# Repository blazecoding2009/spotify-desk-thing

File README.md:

# spotify desk thing
### custom made pcb to be like the [spotify car thing](https://support.spotify.com/us/article/car-thing-discontinued/) (sadly discontinued)

yeah this is something i literally thought of while sitting and listening to music and i think it'd look cool lol
the whole project is pretty self-explanatory, a replacement to the spotify desk think, you could use this as a deskpad with diff firmware too!!

## Features

- ESP32-S3
- 3.5” 480×320 SPI TFT display
- Capacitive touchscreen (GT911)
- SD card music playback
- I²S DAC (PCM5242)
- Differential headphone amp (TPA6132A2)
- Rotary encoder for volume + play/pause
- Headphone output (3.5mm jack)

---

## Hardware Overview

### Main Components

- **ESP32-S3-WROOM-1**
- **ST7796 3.5” TFT Display**
- **GT911 Capacitive Touch (on display)**
- **PCM5242 DAC**
- **TPA6132A2 Headphone Amplifier**
- **MicroSD Card **
- **Rotary Encoder with push button**

## Firmware Overview

The firmware is written using **ESP-IDF**.

### Tasks

- **UI Task**
  - Draws the interface
  - Handles play/pause and volume updates

- **Input Task**
  - Reads touch input
  - Reads rotary encoder events
  - Pushes events into a queue

- **Audio Task**
  - Plays WAV files
  - Handles beeps and stop commands
 
## Future Ideas

- Spotify / Wi-Fi streaming
- Album art
- Playlists
- Battery power
- Better UI animations

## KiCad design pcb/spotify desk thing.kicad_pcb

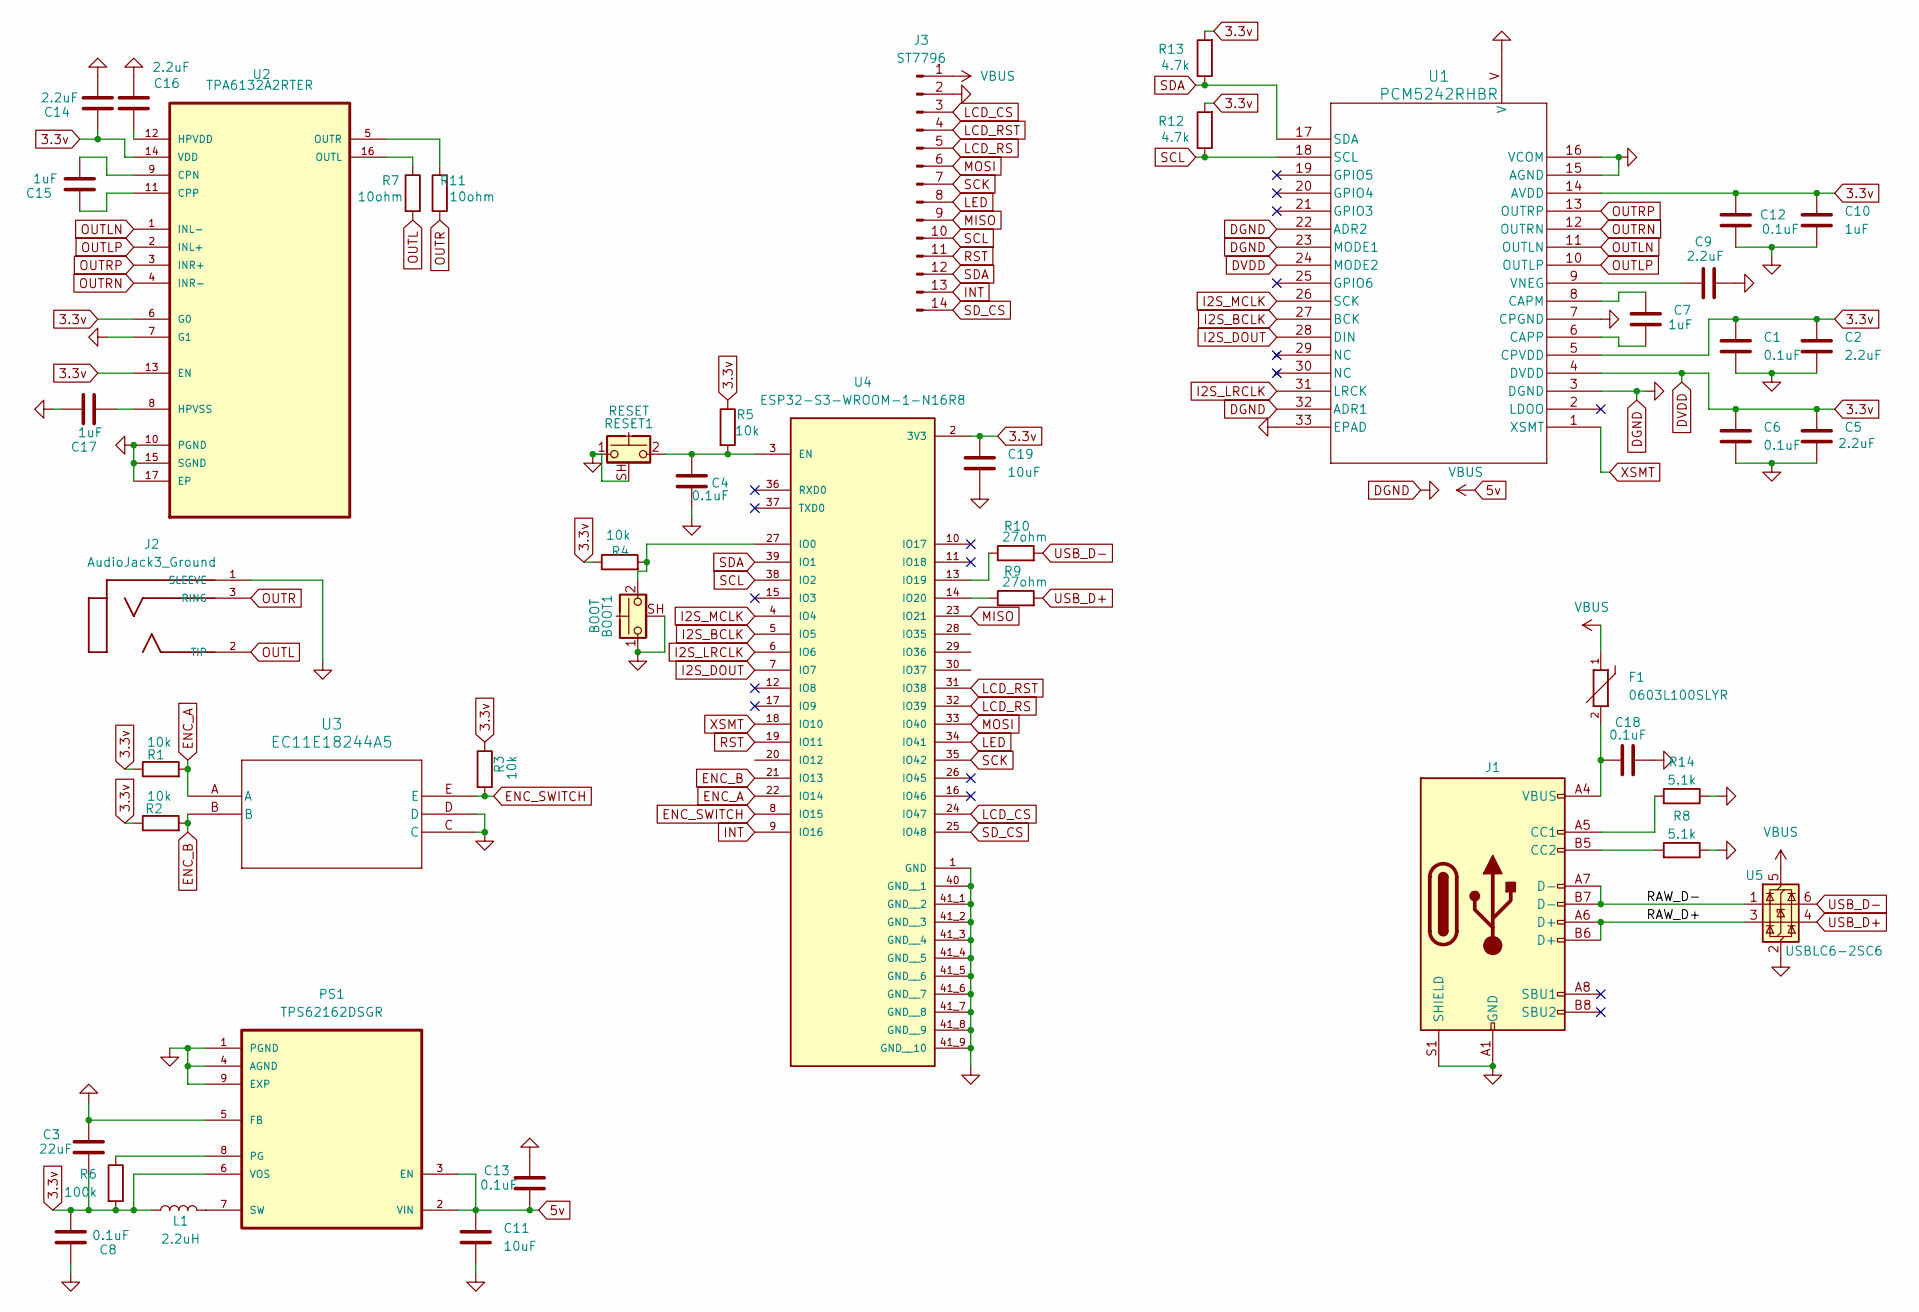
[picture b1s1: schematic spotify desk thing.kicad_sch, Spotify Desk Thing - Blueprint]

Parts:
BOOT1: BOOT; SW_SPST_CK_KMS2xxG; Part # KSR211GLFS; LCSC Part # C221784
C1, C6, C8, C12, C13, C18: 0.1uF; C_0402_1005Metric; Part # TCC0402X5R105K6R3AT; LCSC Part # C1525
C2, C5, C9, C14, C16: 2.2uF; C_0402_1005Metric; Part # TCC0402X5R105K6R3AT; LCSC Part # C12530
C3: 22uF; C_0402_1005Metric; Part # TCC0402X5R105K6R3AT; LCSC Part # C415703
C4: 0.1uF; C_0402_1005Metric; Part # GCM155R71H104KE02J; LCSC Part # C1525
C7, C10, C15: 1uF; C_0402_1005Metric; Part # TCC0402X5R105K6R3AT; LCSC Part # C52923
C11, C19: 10uF; C_0402_1005Metric; Part # TCC0402X5R105K6R3AT; LCSC Part # C15525
C17: 1uF; C_0603_1608Metric; Part # TCC0402X5R105K6R3AT; LCSC Part # C15849
F1: 0603L100SLYR; FUSC1608X100N; PARTREV GD 05.07.21; LCSC Part # C207017
J1: USB_C_Receptacle_USB2.0_16P; USB_C_Receptacle_HRO_TYPE-C-31-M-12; LCSC Part # C165948
J2: AudioJack3_Ground; CUI_SJ-3523-SMT-TR; LCSC Part # C4991872
J3: ST7796; TE_1-1734839-4_1x14-1MP_P0.5mm_Horizontal
L1: 2.2uH; L_0805_2012Metric; Part # WI0805LD101KST-C-HF; LCSC Part # C1043
PS1: TPS62162DSGR; SON50P200X200X80-9N; PARTREV E; LCSC Part # C40256
R1, R3, R4, R5: 10k; R_0603_1608Metric; Part # RC1206JR-134K7L; LCSC Part # C25804
R2: 10k; R_0603_1608Metric; Part # RC1206JR-134K7L; LCSC C25804
R6: 100k; R_0603_1608Metric; Part # RC1206JR-134K7L; LCSC Part # C25803
R7, R11: 10ohm; R_0603_1608Metric; Part # RC1206JR-134K7L; LCSC Part # C22859
R8, R14: 5.1k; R_0402_1005Metric; Part # RMCF0805JT5K10; LCSC Part # C25905
R9, R10: 27ohm; R_0603_1608Metric; Part # RC1206JR-134K7L; LCSC Part # C25190
R12, R13: 4.7k; R_0603_1608Metric; Part # RC1206JR-134K7L; LCSC Part # C23162
RESET1: RESET; SW_SPST_CK_KMS2xxG; Part # KSR211GLFS; LCSC Part # C221784
U1: PCM5242RHBR; RHB32_3P45X3P45_TEX
U2: TPA6132A2RTER; WQFN-16-1EP_3x3mm_P0.5mm_EP1.6x1.6mm_ThermalVias; MPN TPA6132A2RTER
U3: EC11E18244A5; EC11E18244A5_ALPS
U4: ESP32-S3-WROOM-1-N16R8; XCVR_ESP32-S3-WROOM-1-N4; PARTREV v1.0
U5: USBLC6-2SC6; SOT-23-6

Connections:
3.3v: C1.1, C2.1, C3.1, C5.1, C6.1, C8.1, C10.1, C12.1, C14.1, C19.1, L1.1, PS1.6 (VOS), R1.1, R2.1, R3.1, R4.1, R5.1, R6.2, R12.2, R13.2, U1.4 (DVDD), U1.5 (CPVDD), U1.14 (AVDD), U1.24 (MODE2), U2.6 (G0), U2.13 (EN), U2.14 (VDD), U4.2 (3V3)
5v: C11.1, C13.1, F1.1, J3.1, PS1.2 (VIN), PS1.3 (EN), U5.5 (VBUS)
/RAW_D+: J1.A6 (D+), J1.B6 (D+), U5.3 (I/O2)
/RAW_D-: J1.A7 (D-), J1.B7 (D-), U5.1 (I/O1)
DGND: BOOT1.1, BOOT1.SH (B), C1.2, C2.2, C3.2, C4.2, C5.2, C6.2, C8.2, C9.2, C10.2, C11.2, C12.2, C13.2, C14.2, C16.2, C17.1, C18.2, C19.2, J1.A1 (GND), J1.A12 (GND), J1.B1 (GND), J1.B12 (GND), J1.S1 (SHIELD), J2.1 (SLEEVE), J3.2, PS1.1 (PGND), PS1.4 (AGND), PS1.5 (FB), PS1.9 (EXP), R8.1, R14.1, RESET1.1, RESET1.SH (B), U1.3 (DGND), U1.7 (CPGND), U1.15 (AGND), U1.16 (VCOM), U1.22 (ADR2), U1.23 (MODE1), U1.32 (ADR1), U1.33 (EPAD), U1.V, U2.7 (G1), U2.10 (PGND), U2.15 (SGND), U2.17 (EP), U3.C, U3.D, U4.1 (GND), U4.40 (GND__1), U4.41_1 (GND__2), U4.41_2 (GND__3), U4.41_3 (GND__4), U4.41_4 (GND__5), U4.41_5 (GND__6), U4.41_6 (GND__7), U4.41_7 (GND__8), U4.41_8 (GND__9), U4.41_9 (GND__10), U5.2 (GND)
ENC_A: R1.2, U3.A, U4.22 (IO14)
ENC_B: R2.2, U3.B, U4.21 (IO13)
ENC_SWITCH: R3.2, U3.E, U4.8 (IO15)
I2S_BCLK: U1.27 (BCK), U4.5 (IO5)
I2S_DOUT: U1.28 (DIN), U4.7 (IO7)
I2S_LRCLK: U1.31 (LRCK), U4.6 (IO6)
I2S_MCLK: U1.26 (SCK), U4.4 (IO4)
INT: J3.13, U4.9 (IO16)
LCD_CS: J3.3, U4.24 (IO47)
LCD_RS: J3.5, U4.32 (IO39)
LCD_RST: J3.4, U4.31 (IO38)
LED: J3.8, U4.34 (IO41)
MISO: J3.9, U4.23 (IO21)
MOSI: J3.6, U4.33 (IO40)
unnamed: C18.1, F1.2, J1.A4 (VBUS), J1.A9 (VBUS), J1.B4 (VBUS), J1.B9 (VBUS)
unnamed: J1.A5 (CC1), R14.2
unnamed: J1.B5 (CC2), R8.2
unnamed: PS1.8 (PG), R6.1
unnamed: L1.2, PS1.7 (SW)
unnamed: C7.1, U1.8 (CAPM)
unnamed: C7.2, U1.6 (CAPP)
unnamed: C9.1, U1.9 (VNEG)
unnamed: C15.2, U2.9 (CPN)
unnamed: C15.1, U2.11 (CPP)
unnamed: C16.1, U2.12 (HPVDD)
unnamed: C17.2, U2.8 (HPVSS)
unnamed: R7.1, U2.16 (OUTL)
unnamed: R11.1, U2.5 (OUTR)
unnamed: C4.1, R5.2, RESET1.2, U4.3 (EN)
unnamed: BOOT1.2, R4.2, U4.27 (IO0)
unnamed: R10.1, U4.13 (IO19)
unnamed: R9.1, U4.14 (IO20)
OUTL: J2.2 (TIP), R7.2
OUTLN: U1.11 (OUTLN), U2.1 (INL-)
OUTLP: U1.10 (OUTLP), U2.2 (INL+)
OUTR: J2.3 (RING), R11.2
OUTRN: U1.12 (OUTRN), U2.4 (INR-)
OUTRP: U1.13 (OUTRP), U2.3 (INR+)
RST: J3.11, U4.19 (IO11)
SCK: J3.7, U4.35 (IO42)
SCL: J3.10, R12.1, U1.18 (SCL), U4.38 (IO2)
SDA: J3.12, R13.1, U1.17 (SDA), U4.39 (IO1)
SD_CS: J3.14, U4.25 (IO48)
USB_D+: R9.2, U5.4 (I/O2)
USB_D-: R10.2, U5.6 (I/O1)
XSMT: U1.1 (XSMT), U4.18 (IO10)

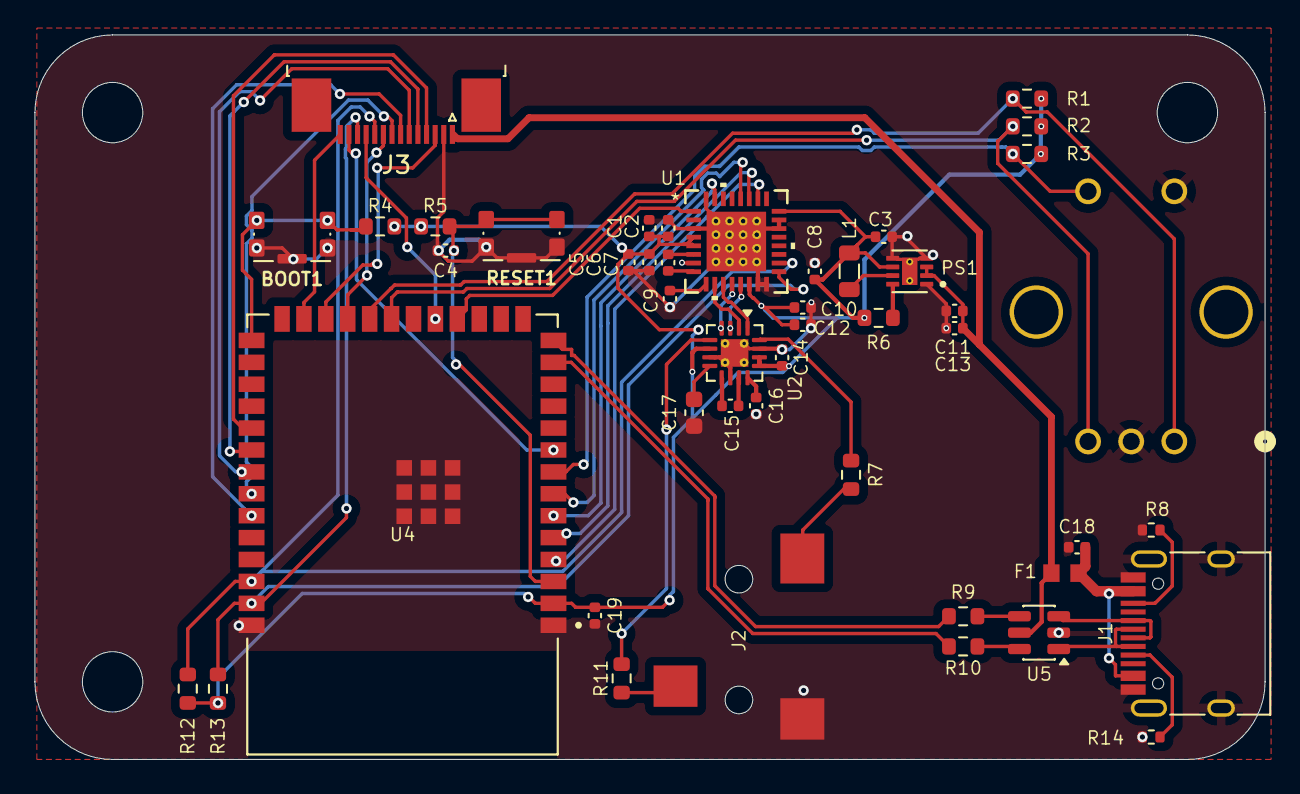
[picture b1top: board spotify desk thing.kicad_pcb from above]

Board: 2 copper layers, 71.3 x 42.0 mm, 46 parts (1 on the bottom side), 51 nets.

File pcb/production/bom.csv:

Designator,Footprint,Quantity,Value,LCSC Part #
BOOT1,SW_SPST_CK_KMS2xxG,1,BOOT,C221784
"C1, C12, C13, C18, C4, C6, C8",0402,7,0.1uF, C1525
"C10, C15, C7",0402,3,1uF,C52923
"C11, C19",0402,2,10uF,C15525
"C14, C16, C2, C5, C9",0402,5,2.2uF,C12530
C17,0603,1,1uF,C15849
C3,0402,1,22uF,C415703
F1,FUSC1608X100N,1,0603L100SLYR,C207017
J1,USB_C_Receptacle_HRO_TYPE-C-31-M-12,1,USB_C_Receptacle_USB2.0_16P, C165948
J2,CUI_SJ-3523-SMT-TR,1,AudioJack3_Ground,C4991872
J3,TE_1-1734839-4_1x14-1MP_P0.5mm_Horizontal,1,ST7796,
L1,0805,1,2.2uH,C1043
PS1,SON50P200X200X80-9N,1,TPS62162DSGR,C40256
"R1, R2, R3, R4, R5",0603,5,10k,C25804
"R10, R9",0603,2,27ohm,C25190
"R11, R7",0603,2,10ohm,C22859
"R12, R13",0603,2,4.7k,C23162
"R14, R8",0402,2,5.1k,C25905
R6,0603,1,100k,C25803
RESET1,SW_SPST_CK_KMS2xxG,1,RESET,C221784
U1,RHB32_3P45X3P45_TEX,1,PCM5242RHBR,
U2,WQFN-16-1EP_3x3mm_P0.5mm_EP1.6x1.6mm_ThermalVias,1,TPA6132A2RTER,TPA6132A2RTER
U3,EC11E18244A5_ALPS,1,EC11E18244A5,
U4,XCVR_ESP32-S3-WROOM-1-N4,1,ESP32-S3-WROOM-1-N16R8,
U5,SOT-23-6,1,USBLC6-2SC6,

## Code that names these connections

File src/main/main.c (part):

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#define SCREEN_DC GPIO_NUM_34
#define SCREEN_RES GPIO_NUM_35
#define SCREEN_BL GPIO_NUM_2
#define SD_CS GPIO_NUM_10

#define I2C_SDA GPIO_NUM_39
#define I2C_SCL GPIO_NUM_38
#define TOUCH_INT GPIO_NUM_9

#define ENC_A GPIO_NUM_18
#define ENC_B GPIO_NUM_17
#define ENC_SW GPIO_NUM_8

#define I2S_MCLK GPIO_NUM_4
#define I2S_BCLK GPIO_NUM_5
#define I2S_LRCLK GPIO_NUM_6
#define I2S_DOUT GPIO_NUM_7

#define MUSIC_DIR "/sd/music"

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
	sdspi_device_config_t slot_config = SDSPI_DEVICE_CONFIG_DEFAULT();
	slot_config.host_id = SPI2_HOST;
	slot_config.gpio_cs = SD_CS;
	slot_config.gpio_cd = SDSPI_SLOT_NO_CD;
	slot_config.gpio_wp = SDSPI_SLOT_NO_WP;

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
static esp_err_t init_encoder(void) {
	encoder_config_t cfg = {
		.pin_a = ENC_A,
		.pin_b = ENC_B,
		.pin_button = ENC_SW,
		.button_active_level_low = true,
		.debounce_ms = 5,
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static esp_err_t init_audio(void) {
	audio_i2s_config_t cfg = {
		.port = I2S_NUM_0,
		.mclk_pin = I2S_MCLK,
		.bclk_pin = I2S_BCLK,
		.lrclk_pin = I2S_LRCLK,
		.dout_pin = I2S_DOUT,
		.sample_rate_hz = 44100,
	};
	return audio_init(&cfg);
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
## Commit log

2026-01-01 creating repo
2026-01-01 wired up 3.3v power and usb c
2026-01-01 bottom file name stuff
2026-01-02 fixed wiring and wired up AMP
2026-01-02 moved stuff around and connected lcd/encoder
2026-01-02 schematic
2026-01-02 deleted unconnected traces
2026-01-02 updated schematic
2026-01-02 routing started
2026-01-02 more routing
2026-01-02 updated stuff to jlc thing
2026-01-02 gitignore/cleanup
2026-01-02 Update license header format
2026-01-02 removed ramdom floating label
2026-01-02 fixed some errors
2026-01-03 cleanup
2026-01-03 Update README with more images
    Added additional images to the README for reference.
2026-01-03 firmware.
2026-01-05 Create BOM.md with pricing information
    Added a Bill of Materials (BOM) with pricing details.
2026-01-05 renaming src to firmware
2026-01-12 updated the stuff to fit the new screen
    Removed old images and added new images for PCB design.
2026-01-12 updated pcb with review changes
2026-01-12 oops forgot smtg
2026-01-12 Enhance README with features and hardware details
    Added features, hardware overview, firmware tasks, and future ideas sections.
2026-01-15 case!
2026-01-15 Update README with additional images
    Added new images to the README for better visualization.
2026-01-15 Update BOM.csv with new components and quantities
    Added new components and updated quantities in BOM.
2026-01-15 Update BOM.csv with new items and costs
2026-01-16 separate case folder
2026-01-16 Enhance README with additional images
    Added images to README for visual reference.
2026-01-21 thinner case
2026-05-02 push
